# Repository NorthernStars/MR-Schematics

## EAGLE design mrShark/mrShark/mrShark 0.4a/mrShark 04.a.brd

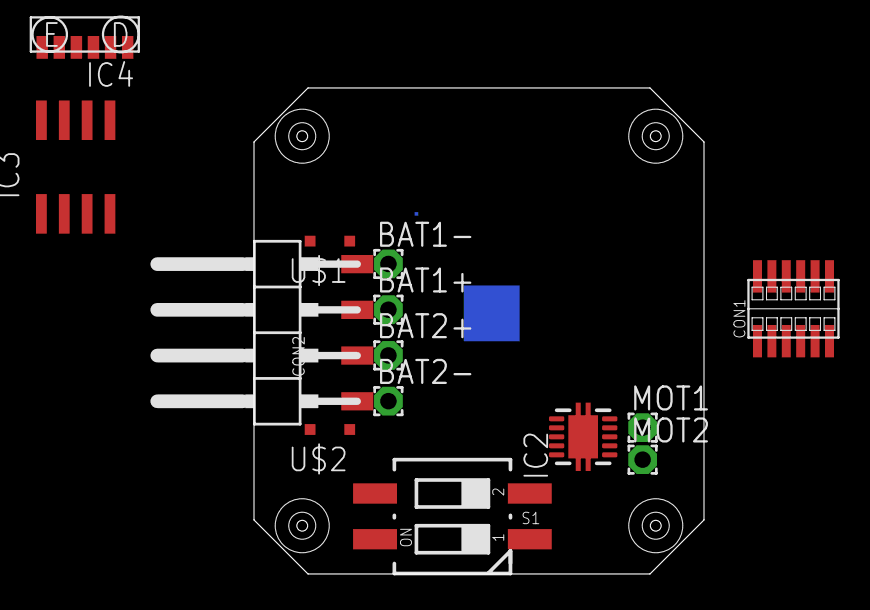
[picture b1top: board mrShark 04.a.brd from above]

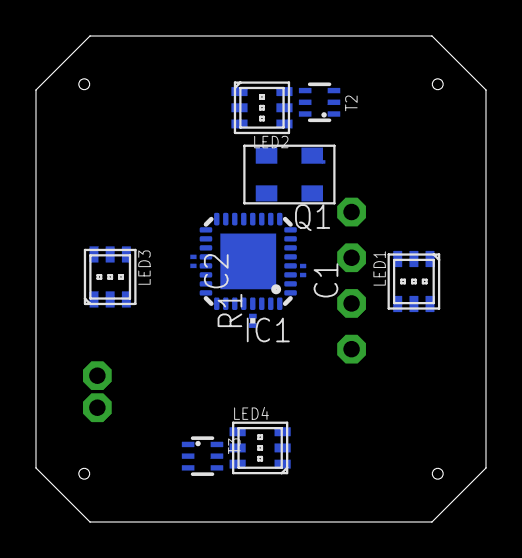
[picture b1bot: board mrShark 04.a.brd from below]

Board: 2 copper layers, 25.0 x 27.0 mm, 29 parts (11 on the bottom side), 29 nets, no tracks yet.

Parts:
BAT1+, BAT1-, BAT2+, BAT2-: 1,6/0,9
C1, C2: 100n; C0201
CON1: 7852-2X6SMT; 7852-2X6
CON2: 1X04SMD/90
H1, H2, H3, H4: MOUNT-HOLE1,5; 1,5
IC1: MEGA48/88/168-MU; MLF32
IC2: DRV8830DGQRWSON; S-PDSO-N10
IC3: TIR1000PSR; SO-08
IC4: TFBS4711TR1; TFBS4711
LED1, LED2, LED3, LED4: ASMT-YTD2-0BB02; PLCC6
MOT1, MOT2: 1,6/0,9
Q1: ASFLM1-1.8432MHZ-L-C-T; MEMS
R1: 1k; R0201
S1: MCEMR-02-T; CTS-219-02
T2, T3: UMX3NTR; SOT363_INFINEON
U$1, U$2: PMEG2010EAR; SOD323-R

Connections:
BAT1+: BAT1+.1, CON2.3, S1.3
BAT1-: BAT1-.1, CON2.4, U$1.C
BAT2+: BAT2+.1, CON2.2, S1.4
BAT2-: BAT2-.1, CON2.1, U$2.C
CLK: IC1.7, IC3.1, Q1.3
GND: C1.2, C2.2, IC1.3, IC1.5, IC1.21, IC2.5, IC2.7, IC2.8, IC2.PP, IC2.PP@1, IC2.PP@2, IC3.4, IC3.5, IC4.6, Q1.2, U$1.A, U$2.A
IR_SD: IC1.2, IC4.4
LED1: IC1.23, T2.2
LED1+: LED1.4, LED1.5, LED1.6, T2.1
LED2: IC1.24, T2.3
LED2+: LED2.4, LED2.5, LED2.6, T2.5
LED3: IC1.25, T3.2
LED3+: LED3.4, LED3.5, LED3.6, T3.1
LED4: IC1.26, T3.3
LED4+: LED4.4, LED4.5, LED4.6, T3.5
LED_B: IC1.11, LED1.1, LED2.1, LED3.1, LED4.1
LED_G: IC1.10, LED1.2, LED2.2, LED3.2, LED4.2
LED_R: IC1.9, LED1.3, LED2.3, LED3.3, LED4.3
unnamed: C2.1, IC1.20
unnamed: IC2.3, MOT1.1
unnamed: IC2.1, MOT2.1
RESET: IC1.29, R1.2
RXD: IC1.30, IC3.3
RXIR: IC3.6, IC4.3
SCL: IC1.28, IC2.10
SDA: IC1.27, IC2.9
TXD: IC1.31, IC3.2
TXIR: IC3.7, IC4.2
VCC: C1.1, IC1.4, IC1.6, IC1.18, IC2.4, IC3.8, IC4.5, Q1.1, Q1.4, R1.1, S1.1, S1.2, T2.4, T2.6, T3.4, T3.6

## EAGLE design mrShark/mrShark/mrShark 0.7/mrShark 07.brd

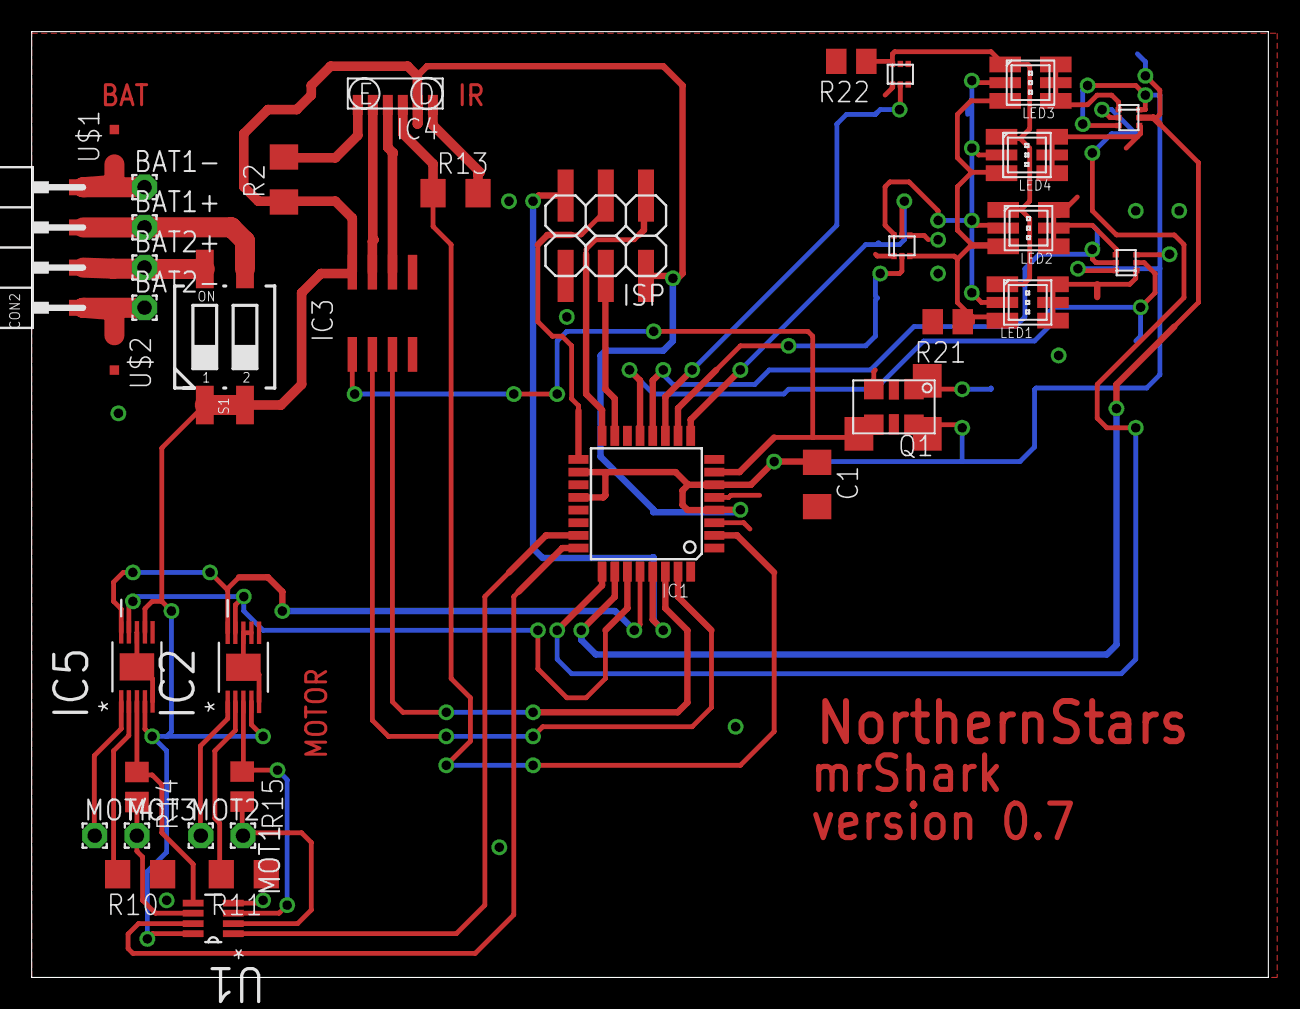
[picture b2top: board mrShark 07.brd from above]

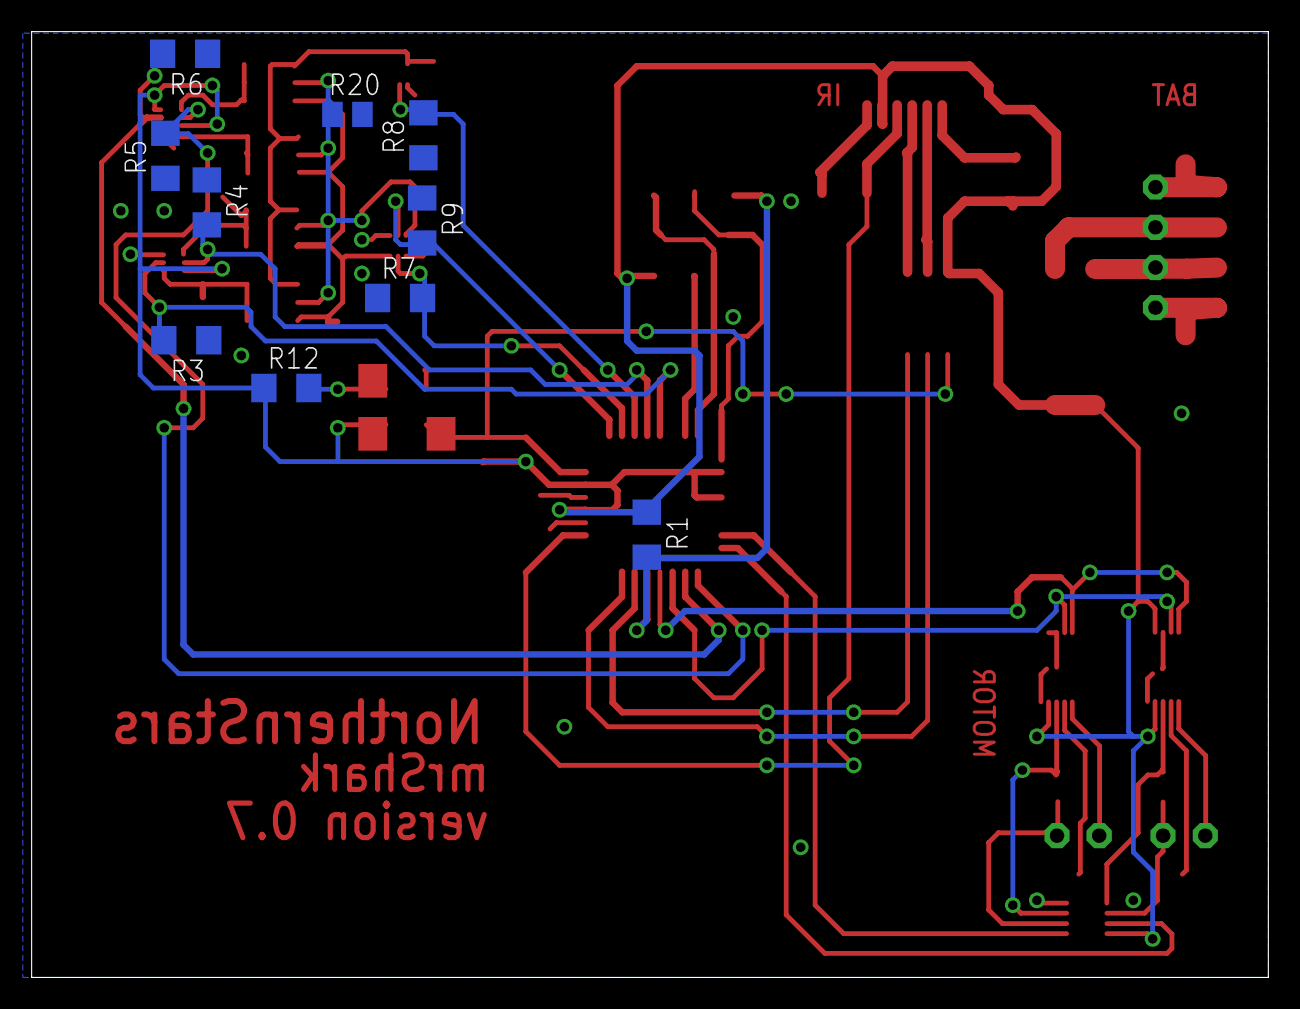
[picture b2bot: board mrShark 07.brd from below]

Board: 2 copper layers, 78.2 x 59.8 mm, 47 parts (10 on the bottom side), 44 nets.

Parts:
BAT1+, BAT1-, BAT2+, BAT2-: 1,6/0,9
C1: 100n; C1206
CON2: 1X04SMD/90
IC1: MEGA48/88/168-AU; TQFP32-08
IC2, IC5: DRV8830DGQRMSOP; SOP65P640X110-15N
IC3: TIR1000PSR; SO-08
IC4: TFBS4711TR1; TFBS4711
ISP: 2X03SMD
LED1, LED2, LED3, LED4: ASMT-YTD2-0BB02; PLCC6K
MOT1, MOT2, MOT3, MOT4: 1,6/0,9
Q1: ASFLM1-1.8432MHZ-L-C-T; HC536
R1, R3, R4, R5, R6, R7, R8, R9, R12, R13: 1k; R1206
R2: 27R; R1206
R10, R11: 0.95R; R1206
R14, R15: 0R2; R0805
R20, R21, R22: 10k; M0805
S1: MCEMR-02-T; CTS-219-02
T1, T2, T3, T4: FC694601R; SOT-666
U1: OPA2348AIDCNTG4; SOT65P280X145-8N
U$1, U$2: PMEG2010EAR; SOD323-R

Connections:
BAT1+: BAT1+.1, CON2.3, S1.3
BAT1-: BAT1-.1, CON2.4, U$1.C
BAT2+: BAT2+.1, CON2.2, S1.4
BAT2-: BAT2-.1, CON2.1, U$2.C
CLK: IC1.7, IC3.1, Q1.3
COLOR_B: LED1.1, LED2.1, LED3.1, LED4.1, R22.1, T4.6
COLOR_G: LED1.2, LED2.2, LED3.2, LED4.2, R20.1, T3.6
COLOR_R: LED1.3, LED2.3, LED3.3, LED4.3, R21.1, T3.3
GND: C1.2, IC1.3, IC1.5, IC1.21, IC2.5, IC2.7, IC2.8, IC2.11, IC3.4, IC3.5, IC4.6, IC5.5, IC5.8, IC5.11, ISP.6, Q1.2, R3.1, R4.1, R5.1, R6.1, R7.1, R8.1, R9.1, R10.1, R11.1, R13.2, T3.1, T3.4, T4.1, U1.4, U$1.A, U$2.A
IRDA: IC4.1, R2.2
IR_SD: IC1.2, IC4.4, R13.1
ISENS_MOTL: IC1.23, U1.1
ISENS_MOTR: IC1.24, U1.7
LED1: IC1.13, R3.2, T1.2
LED1+: LED1.4, LED1.5, LED1.6, T1.1
LED2: IC1.12, R4.2, T1.5
LED2+: LED2.4, LED2.5, LED2.6, T1.4
LED3: IC1.25, R5.2, T2.2
LED3+: LED3.4, LED3.5, LED3.6, T2.1
LED4: IC1.26, R6.2, T2.5
LED4+: LED4.4, LED4.5, LED4.6, T2.4
LED_B: IC1.11, R8.2, T4.2
LED_G: IC1.10, R7.2, T3.2
LED_R: IC1.9, R9.2, T3.5
MISO: IC1.16, ISP.1
MOSI: IC1.15, ISP.4
unnamed: IC5.1, MOT4.1
unnamed: Q1.1, R12.2
unnamed: IC5.2, R10.2
unnamed: IC2.2, R11.2
unnamed: IC2.1, MOT2.1
RESET: IC1.29, ISP.5, R1.2
RXD: IC1.30, IC3.3
RXIR: IC3.6, IC4.3
SCK: IC1.17, ISP.3
SCL: IC1.28, IC2.10, IC5.10
SDA: IC1.27, IC2.9, IC5.9
SENS_MOTL1: IC2.3, R15.1, U1.3
SENS_MOTL2: MOT1.1, R15.2, U1.2
SENS_MOTR1: IC5.3, R14.1, U1.5
SENS_MOTR2: MOT3.1, R14.2, U1.6
TXD: IC1.31, IC3.2
TXIR: IC3.7, IC4.2
VCC: C1.1, IC1.4, IC1.6, IC1.18, IC1.20, IC2.4, IC3.8, IC4.5, IC5.4, IC5.7, ISP.2, Q1.4, R1.1, R2.1, R12.1, R20.2, R21.2, R22.2, S1.1, S1.2, T1.3, T1.6, T2.3, T2.6, U1.8

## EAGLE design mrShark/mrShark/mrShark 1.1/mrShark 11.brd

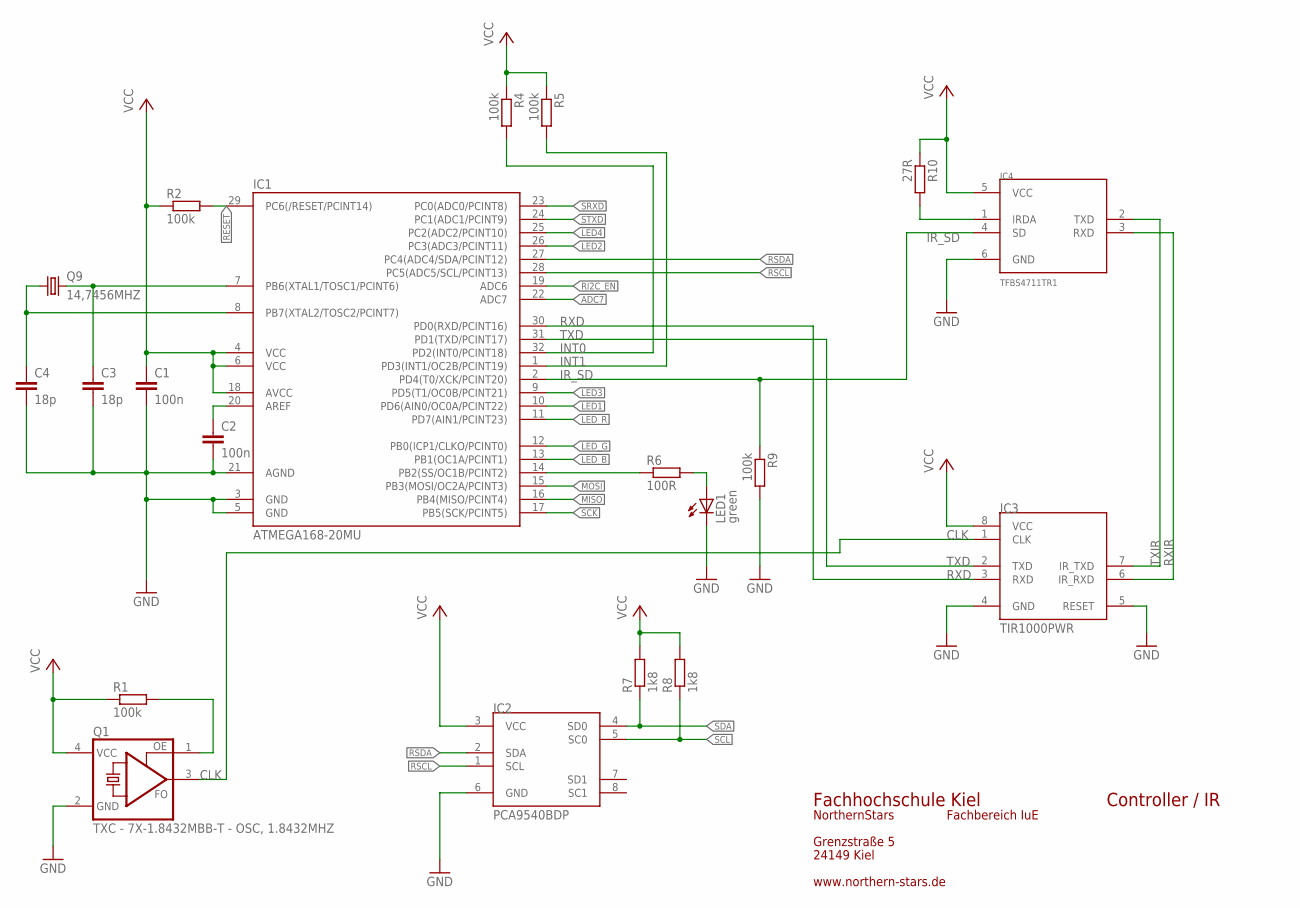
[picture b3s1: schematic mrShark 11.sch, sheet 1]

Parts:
C1, C2: 100n; C0201
C3, C4: 18p; C0201
IC1: ATMEGA168-20MU; MLF32
IC2: PCA9540BDP; TSSOP8
IC3: TIR1000PWR; PW_R-PDSO-G08
IC4: TFBS4711TR1; TFBS4711
LED1: green; CHIPLED_0603
Q1: TXC - 7X-1.8432MBB-T - OSC, 1.8432MHZ; 3.2X2.5
Q9: 14,7456MHZ; TXC_7B_SERIES
R1, R2, R4, R5, R9: 100k; R0201
R6: 100R; R0201
R7, R8: 1k8; R0201
R10: 27R; R0201

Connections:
ADC7: IC1.22 (ADC7); also elsewhere on the board
CLK: IC3.1 (CLK), Q1.3 (FO)
GND: C1.2, C2.2, C3.2, C4.2, IC1.3 (GND), IC1.5 (GND), IC1.21 (AGND), IC2.6 (GND), IC3.4 (GND), IC3.5 (RESET), IC4.6 (GND), LED1.C, Q1.2 (GND), R9.2; also elsewhere on the board
INT0: IC1.32 (PD2(INT0/PCINT18)), R4.2; also elsewhere on the board
INT1: IC1.1 (PD3(INT1/OC2B/PCINT19)), R5.2; also elsewhere on the board
IRDA: IC4.1 (IRDA), R10.2
IR_SD: IC1.2 (PD4(T0/XCK/PCINT20)), IC4.4 (SD), R9.1
LED1: IC1.10 (PD6(AIN0/OC0A/PCINT22)); also elsewhere on the board
LED2: IC1.26 (PC3(ADC3/PCINT11)); also elsewhere on the board
LED3: IC1.9 (PD5(T1/OC0B/PCINT21)); also elsewhere on the board
LED4: IC1.25 (PC2(ADC2/PCINT10)); also elsewhere on the board
LED_B: IC1.13 (PB1(OC1A/PCINT1)); also elsewhere on the board
LED_G: IC1.12 (PB0(ICP1/CLKO/PCINT0)); also elsewhere on the board
LED_R: IC1.11 (PD7(AIN1/PCINT23)); also elsewhere on the board
MISO: IC1.16 (PB4(MISO/PCINT4)); also elsewhere on the board
MOSI: IC1.15 (PB3(MOSI/OC2A/PCINT3)); also elsewhere on the board
unnamed: IC1.14 (PB2(SS/OC1B/PCINT2)), R6.1
unnamed: Q1.1 (OE), R1.2
unnamed: LED1.A, R6.2
unnamed: C2.1, IC1.20 (AREF)
RESET: IC1.29 (PC6(/RESET/PCINT14)), R2.2; also elsewhere on the board
RI2C_EN: IC1.19 (ADC6)
RSCL: IC1.28 (PC5(ADC5/SCL/PCINT13)), IC2.1 (SCL); also elsewhere on the board
RSDA: IC1.27 (PC4(ADC4/SDA/PCINT12)), IC2.2 (SDA); also elsewhere on the board
RXD: IC1.30 (PD0(RXD/PCINT16)), IC3.3 (RXD)
RXIR: IC3.6 (IR_RXD), IC4.3 (RXD)
SCK: IC1.17 (PB5(SCK/PCINT5)); also elsewhere on the board
SCL: IC2.5 (SC0), R8.1; also elsewhere on the board
SDA: IC2.4 (SD0), R7.1; also elsewhere on the board
SRXD: IC1.23 (PC0(ADC0/PCINT8)); also elsewhere on the board
STXD: IC1.24 (PC1(ADC1/PCINT9)); also elsewhere on the board
TXD: IC1.31 (PD1(TXD/PCINT17)), IC3.2 (TXD)
TXIR: IC3.7 (IR_TXD), IC4.2 (TXD)
VCC: C1.1, IC1.4 (VCC), IC1.6 (VCC), IC1.18 (AVCC), IC2.3 (VCC), IC3.8 (VCC), IC4.5 (VCC), Q1.4 (VCC), R1.1, R2.1, R4.1, R5.1, R7.2, R8.2, R10.1; also elsewhere on the board
XTAL1: C3.1, IC1.7 (PB6(XTAL1/TOSC1/PCINT6)), Q9.3 (2)
XTAL2: C4.1, IC1.8 (PB7(XTAL2/TOSC2/PCINT7)), Q9.1

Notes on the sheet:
Fachhochschule Kiel
Grenzstraße 5
24149 Kiel
NorthernStars
Fachbereich IuE
www.northern-stars.de
Controller / IR

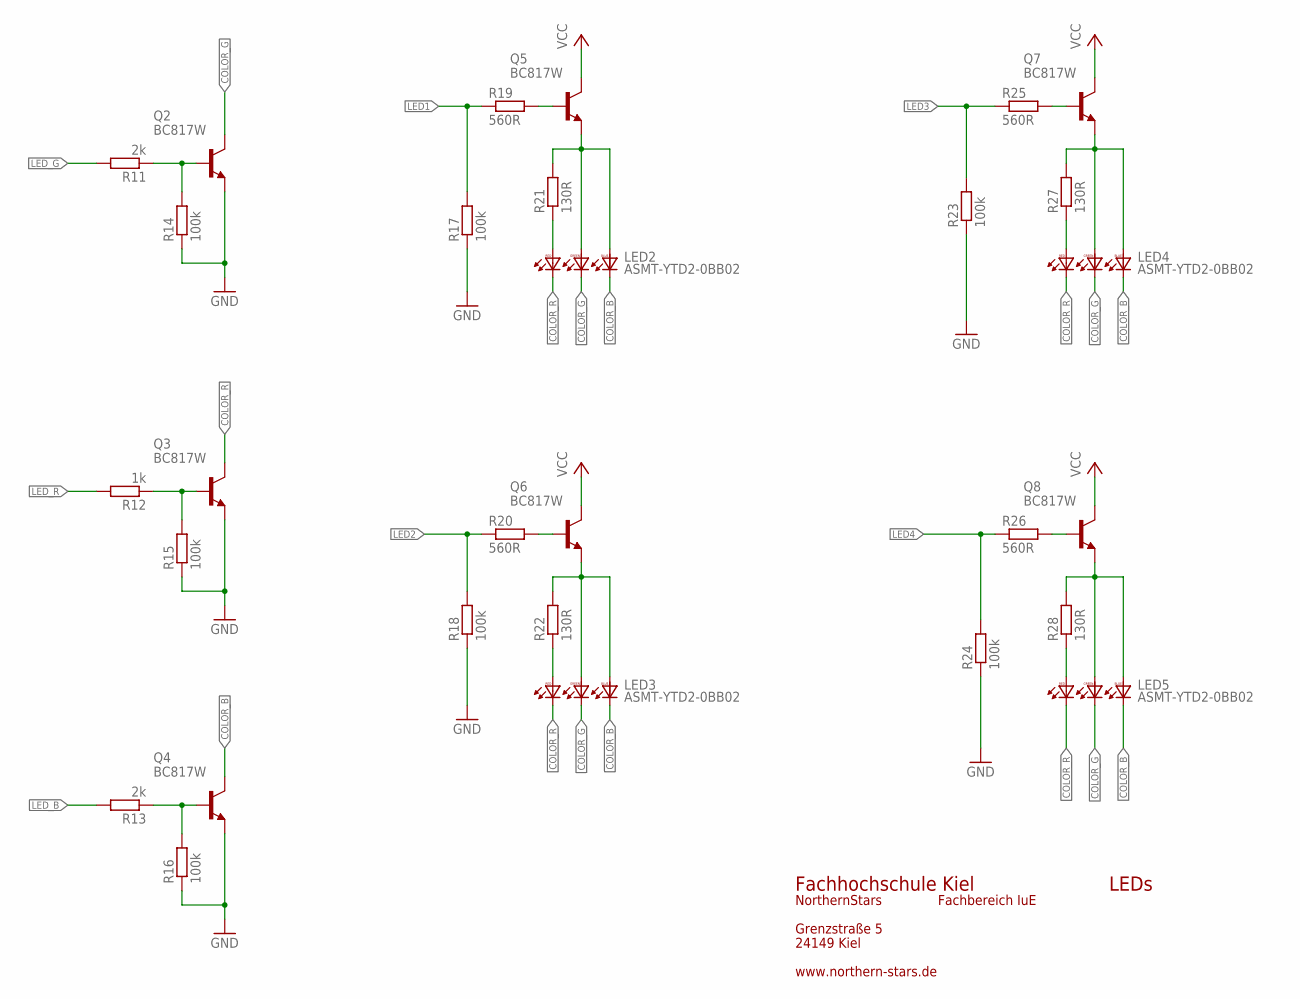
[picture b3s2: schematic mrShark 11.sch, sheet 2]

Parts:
LED2, LED3, LED4, LED5: ASMT-YTD2-0BB02; PLCC6K
Q2, Q3, Q4, Q5, Q6, Q7, Q8: BC817W; SOT323-BEC
R11, R13: 2k; R0201
R12: 1k; R0201
R14, R15, R16, R17, R18, R23, R24: 100k; R0201
R19, R20, R25, R26: 560R; R0201
R21, R22, R27, R28: 130R; R0201

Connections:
COLOR_B: LED2.1 (BC), LED3.1 (BC), LED4.1 (BC), LED5.1 (BC), Q4.C
COLOR_G: LED2.2 (GC), LED3.2 (GC), LED4.2 (GC), LED5.2 (GC), Q2.C
COLOR_R: LED2.3 (RC), LED3.3 (RC), LED4.3 (RC), LED5.3 (RC), Q3.C
GND: Q2.E, Q3.E, Q4.E, R14.1, R15.1, R16.1, R17.1, R18.1, R23.1, R24.1; also elsewhere on the board
LED1: R17.2, R19.1; also elsewhere on the board
LED2: R18.2, R20.1; also elsewhere on the board
LED3: R23.2, R25.1; also elsewhere on the board
LED4: R24.2, R26.1; also elsewhere on the board
LED_B: R13.2; also elsewhere on the board
LED_G: R11.2; also elsewhere on the board
LED_R: R12.2; also elsewhere on the board
unnamed: LED2.4 (RA), R21.1
unnamed: LED4.4 (RA), R27.1
unnamed: LED4.5 (GA), LED4.6 (BA), Q7.E, R27.2
unnamed: LED3.4 (RA), R22.1
unnamed: LED3.5 (GA), LED3.6 (BA), Q6.E, R22.2
unnamed: Q6.B, R20.2
unnamed: LED5.4 (RA), R28.1
unnamed: LED5.5 (GA), LED5.6 (BA), Q8.E, R28.2
unnamed: Q8.B, R26.2
unnamed: Q7.B, R25.2
unnamed: Q5.B, R19.2
unnamed: LED2.5 (GA), LED2.6 (BA), Q5.E, R21.2
VCC: Q5.C, Q6.C, Q7.C, Q8.C; also elsewhere on the board
X1: Q4.B, R13.1, R16.2
X2: Q3.B, R12.1, R15.2
X3: Q2.B, R11.1, R14.2

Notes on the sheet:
LEDs
Fachhochschule Kiel
Grenzstraße 5
24149 Kiel
NorthernStars
Fachbereich IuE
www.northern-stars.de

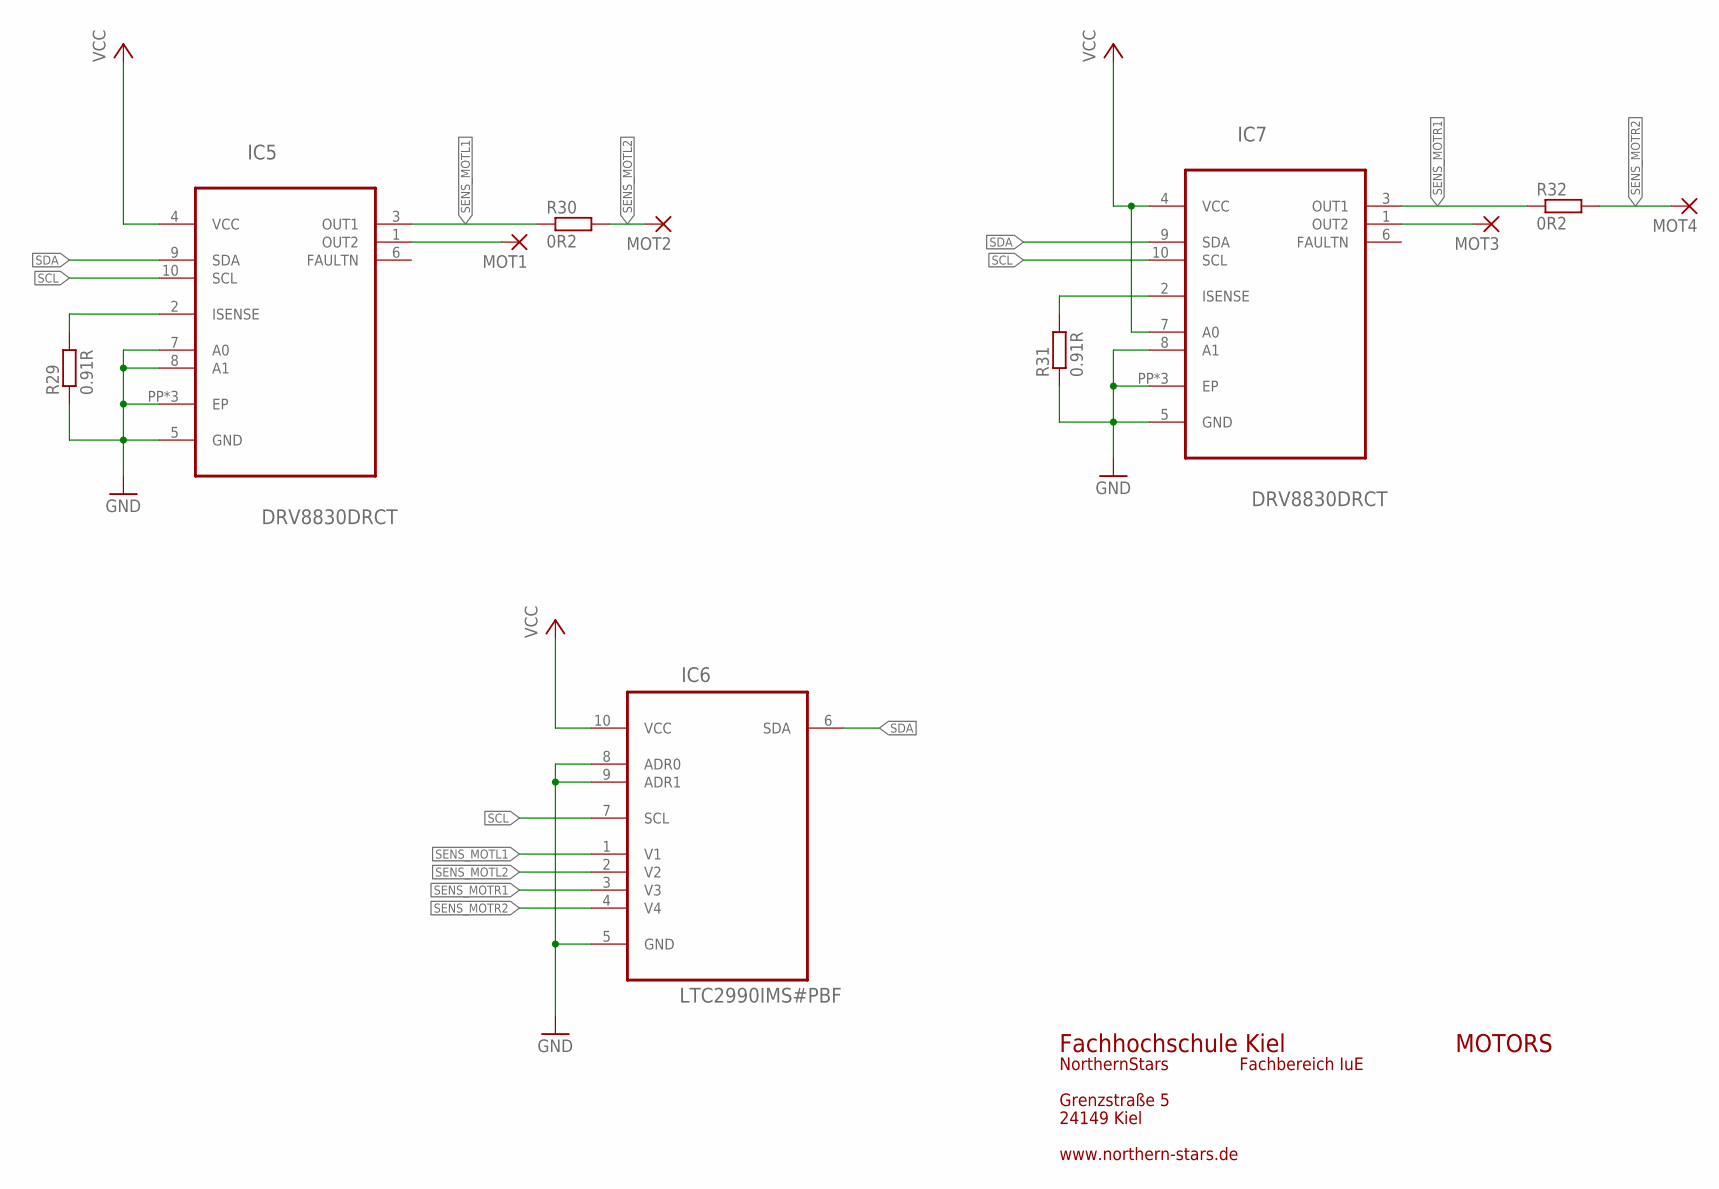
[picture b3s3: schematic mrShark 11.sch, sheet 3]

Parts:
IC5, IC7: DRV8830DRCT; S-PDSO-N10
IC6: LTC2990IMS#PBF; SOP50P490X110-10N
MOT1, MOT2, MOT3, MOT4: 1,6/0,9
R29, R31: 0.91R; R0603
R30, R32: 0R2; R0603

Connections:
GND: IC5.5 (GND), IC5.7 (A0), IC5.8 (A1), IC5.PP (EP), IC5.PP@1 (EP), IC5.PP@2 (EP), IC6.5 (GND), IC6.8 (ADR0), IC6.9 (ADR1), IC7.5 (GND), IC7.8 (A1), IC7.PP (EP), IC7.PP@1 (EP), IC7.PP@2 (EP), R29.1, R31.1; also elsewhere on the board
unnamed: IC5.1 (OUT2), MOT1.1
unnamed: IC5.2 (ISENSE), R29.2
unnamed: IC7.1 (OUT2), MOT3.1
unnamed: IC7.2 (ISENSE), R31.2
SCL: IC5.10 (SCL), IC6.7 (SCL), IC7.10 (SCL); also elsewhere on the board
SDA: IC5.9 (SDA), IC6.6 (SDA), IC7.9 (SDA); also elsewhere on the board
SENS_MOTL1: IC5.3 (OUT1), IC6.1 (V1), R30.1
SENS_MOTL2: IC6.2 (V2), MOT2.1, R30.2
SENS_MOTR1: IC6.3 (V3), IC7.3 (OUT1), R32.1
SENS_MOTR2: IC6.4 (V4), MOT4.1, R32.2
VCC: IC5.4 (VCC), IC6.10 (VCC), IC7.4 (VCC), IC7.7 (A0); also elsewhere on the board

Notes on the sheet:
MOTORS
Fachhochschule Kiel
Grenzstraße 5
24149 Kiel
NorthernStars
Fachbereich IuE
www.northern-stars.de

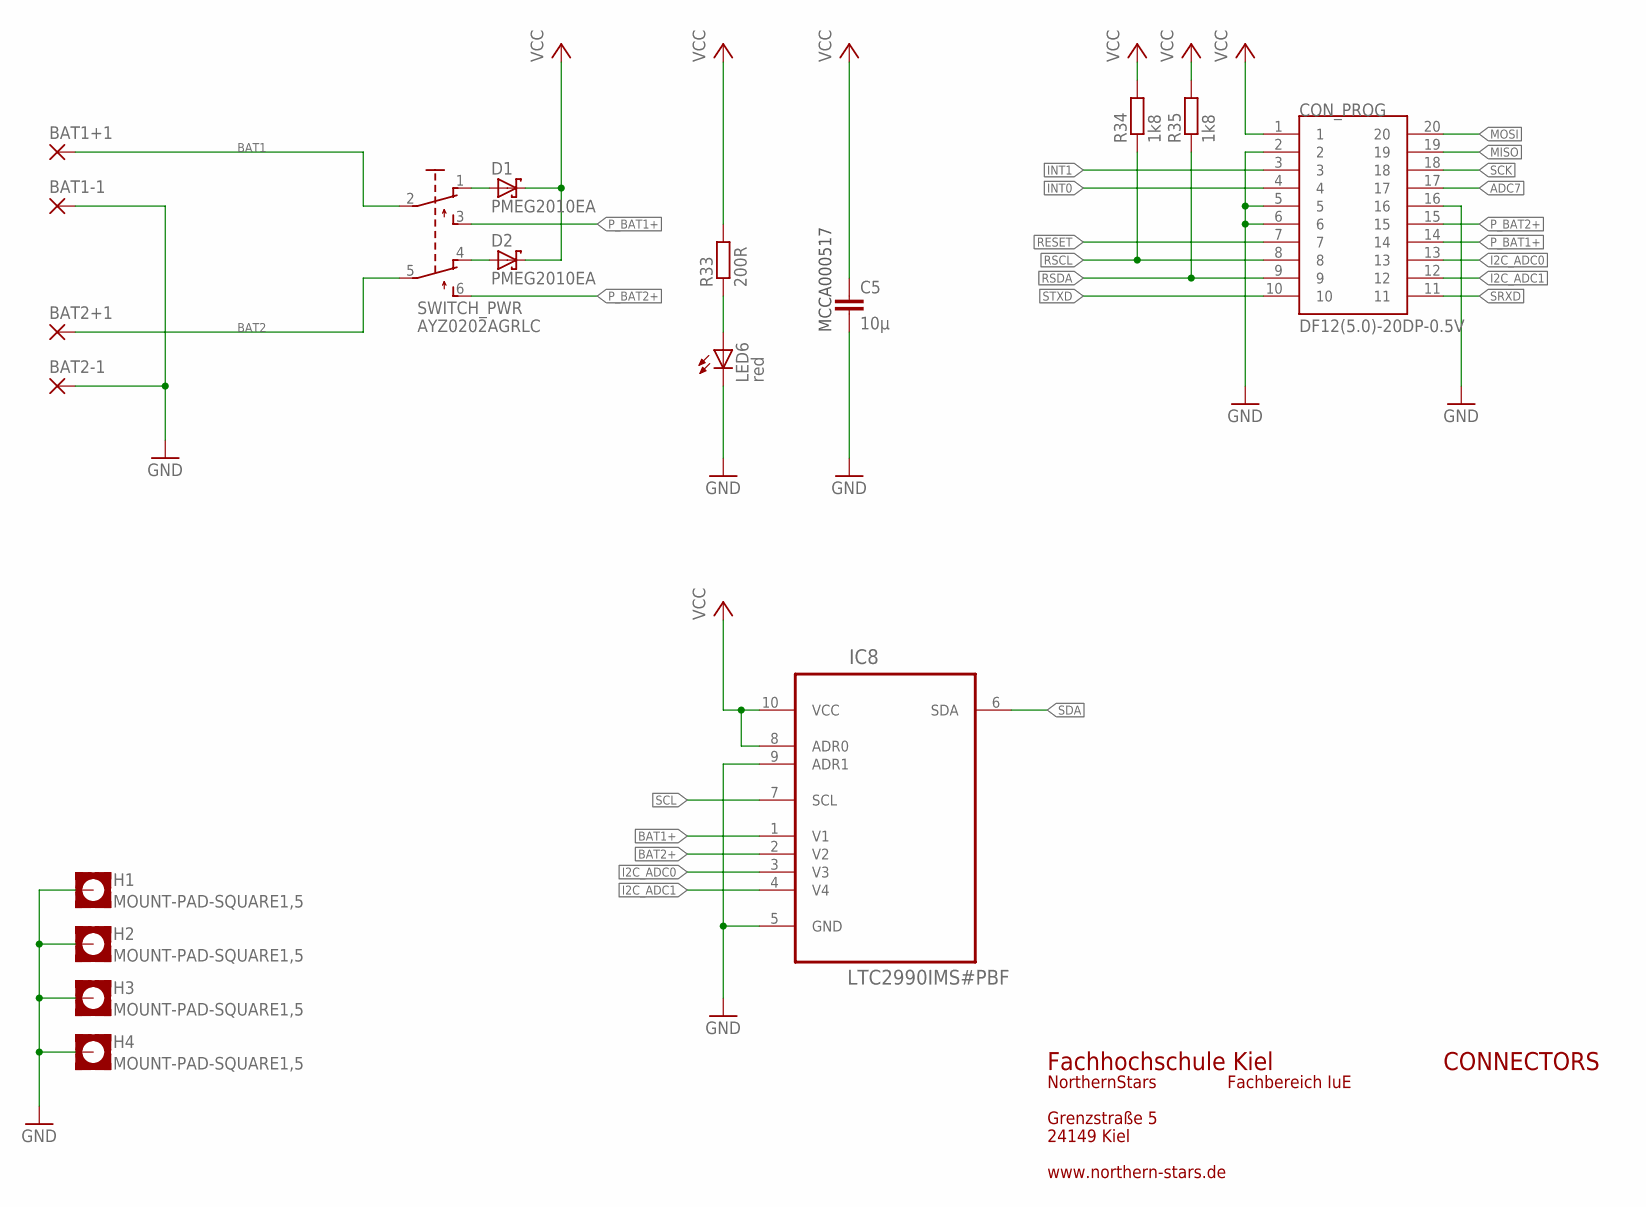
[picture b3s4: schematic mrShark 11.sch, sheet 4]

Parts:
BAT1+1, BAT1-1, BAT2+1, BAT2-1: 1,6/0,9
C5: 10µ; C0603K
CON_PROG: DF12(5.0)-20DP-0.5V; DF12-20DP
D1, D2: PMEG2010EA; SOD323-R
H1, H2, H3, H4: MOUNT-PAD-SQUARE1,5; 0,75-PAD-SQUARE
IC8: LTC2990IMS#PBF; SOP50P490X110-10N
LED6: red; CHIPLED_0603
R33: 200R; R0201
R34, R35: 1k8; R0201
SWITCH_PWR: AYZ0202AGRLC; AYZ0202AGLRC

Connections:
ADC7: CON_PROG.17; also elsewhere on the board
BAT1: BAT1+1.1, SWITCH_PWR.2
BAT1+: D1.A, IC8.1 (V1), SWITCH_PWR.1 (O)
BAT2: BAT2+1.1, SWITCH_PWR.5 (P1)
BAT2+: D2.A, IC8.2 (V2), SWITCH_PWR.4 (O1)
GND: BAT1-1.1, BAT2-1.1, C5.2, CON_PROG.2, CON_PROG.5, CON_PROG.6, CON_PROG.16, H1.P, H2.P, H3.P, H4.P, IC8.5 (GND), IC8.9 (ADR1), LED6.C; also elsewhere on the board
I2C_ADC0: CON_PROG.13, IC8.3 (V3)
I2C_ADC1: CON_PROG.12, IC8.4 (V4)
INT0: CON_PROG.4; also elsewhere on the board
INT1: CON_PROG.3; also elsewhere on the board
MISO: CON_PROG.19; also elsewhere on the board
MOSI: CON_PROG.20; also elsewhere on the board
unnamed: LED6.A, R33.1
P_BAT1+: CON_PROG.14, SWITCH_PWR.3 (S)
P_BAT2+: CON_PROG.15, SWITCH_PWR.6 (S1)
RESET: CON_PROG.7; also elsewhere on the board
RSCL: CON_PROG.8, R34.1; also elsewhere on the board
RSDA: CON_PROG.9, R35.1; also elsewhere on the board
SCK: CON_PROG.18; also elsewhere on the board
SCL: IC8.7 (SCL); also elsewhere on the board
SDA: IC8.6 (SDA); also elsewhere on the board
SRXD: CON_PROG.11; also elsewhere on the board
STXD: CON_PROG.10; also elsewhere on the board
VCC: C5.1, CON_PROG.1, D1.C, D2.C, IC8.8 (ADR0), IC8.10 (VCC), R33.2, R34.2, R35.2; also elsewhere on the board

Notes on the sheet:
CONNECTORS
Fachhochschule Kiel
Grenzstraße 5
24149 Kiel
NorthernStars
Fachbereich IuE
www.northern-stars.de
MCCA000517

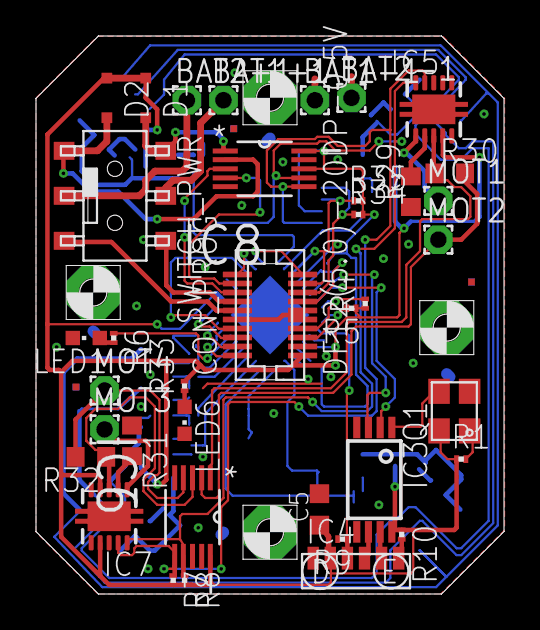
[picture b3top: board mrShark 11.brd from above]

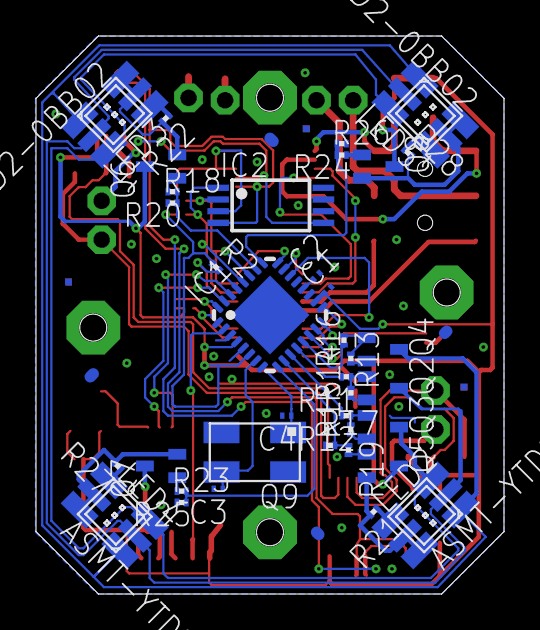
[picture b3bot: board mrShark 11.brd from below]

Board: 2 copper layers, 26.0 x 31.0 mm, 78 parts (37 on the bottom side), 70 nets.

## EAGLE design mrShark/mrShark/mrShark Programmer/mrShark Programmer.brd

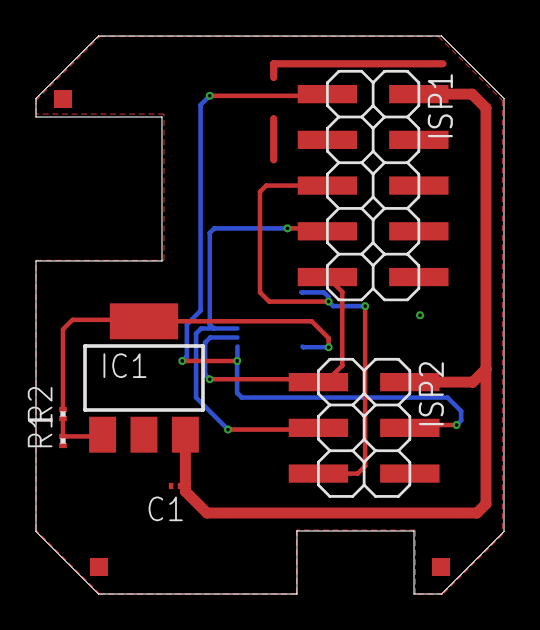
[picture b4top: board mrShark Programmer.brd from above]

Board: 2 copper layers, 26.0 x 31.0 mm, 7 parts (1 on the bottom side), 8 nets.

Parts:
C1: 100n; C0201
CON: DF12-20DS
IC1: LM317MBSTT3; SOT223
ISP1: TSM-105-04-T-DV; 2X05SMD
ISP2: TSM-103-04-T-DV; 2X03SMD
R1: 165k; R0201
R2: 100k; R0201

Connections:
+5V: C1.1, IC1.3, ISP1.2, ISP2.2
GND: C1.2, CON.6, CON.12, CON.15, CON.16, ISP1.4, ISP1.6, ISP1.8, ISP1.10, ISP2.6, R1.1
MISO: CON.9, ISP1.9, ISP2.1
MOSI: CON.10, ISP1.1, ISP2.4
unnamed: IC1.1, R1.2, R2.1
RESET: CON.17, ISP1.5, ISP2.5
SCK: CON.8, ISP1.7, ISP2.3
VCC: CON.11, IC1.4, R2.2
